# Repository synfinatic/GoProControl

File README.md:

# GoProControl

## About

I wanted an easy way to syncronize my GoPro videos with the data generated from
my data logger.  In the past, I've done this manually with
[DashWare](http://www.dashware.net), but it is a tedious manual process to get
them syncronized.  There had to be a better way!

I realized that many GoPro's (GoPro3 Silver/Black, GoPro4, etc) have built in
WiFi and we all know about the iPhone and Android apps.  So clearly there was a
way to controll them via WiFi.

GoProControl is a simple box you can plug into your car or motorcycle and
connect to your datalogger's digital output or input sensor.  I use the
inexpensive [ESP8266](http://www.esp8266.com/) to control the a GoPro.  In the
future, I hope to be able to control multiple GoPro's like the [GoPro
Remote](http://shop.gopro.com/accessories/smart-remote/ARMTE-002.html) can.

## How it works

GoProControl has 4 pins:

 1. +5-12V
 2. GND
 3. Digital Input 
 4. Digital Ouput
 
When GoProControl is turned on, it will send a signal to the GoPro to also turn
on- which may take a few seconds.  When the Digital Input is connected to
ground (GND) it will tell the GoPro to start recording. 

When the Digital Input is disconnected from ground (floating or +3.3-12V) it
will tell the GoPro to stop recording.  You should configure your GoPro to
auto-off after 60seconds to save battery.

Note, when the Digital Input is connected to ground, the Digital Output will be
driven to 3.3V.  This is so if your data logger does not have an output channel
you can control, you can use a simple toggle switch to both turn on the GoPro
and mark the time when recording started in your data logger using an input
channel on your data logger.

**Note:** If you have the option of powering this by 5 or 12V, use 5V.  If
using your vehicle's battery, be sure it is switched with the ignition to
prevent draining your battery as this circuit uses ~330mA.

## Programming

The GoProControl board has an onboard connector for programming via a FTDI
cable.  This cable should provide 5V of power and can use either 3.3V or 
5V for signalling.

Configure your GoPro WiFi for "App Mode" and define a SSID and WiFi Password.

Before programming your GoProController, you first need to edit 
**src/goprocontrol/goprocontrol.ino** and edit the SSID and WIFI_PASSWORD
to match your GoPro's settings.

In order to program your GoProController, you will need to start the Arduino
application and figure out what serial speed (baud) your ESP8266 communicates
at.  Older boards run at 9600, while newer boards seem to run at 115200.  

Once you have figured out the serial speed, configure Arduino for a 
"Generic ESP8266 Module" and the upload speed to the same speed.  Then, 
with the board powered up:

 1. Press and hold the PROG button
 2. Press and release the RST button
 3. Release the PROG button
 4. Uplaod the sketch via the Arduino application

## Links Links to projects or information that was critical to me creating this
project.  Thank you!

 * [GoProWiFiHack](https://github.com/KonradIT/goprowifihack)
 * [GoProController](https://github.com/joshvillbrandt/GoProController)
 * [GoProHero](https://github.com/joshvillbrandt/goprohero)
 * [GoProControllerUI](https://github.com/joshvillbrandt/GoProControllerUI)

## License

GoProControl is GPLv3

## Trademarks

GoPro, GoPro3 and GoPro4 are trademark [GoPro](http://www.gopro.com).

GoProControl is not affiliated with GoPro in any way.

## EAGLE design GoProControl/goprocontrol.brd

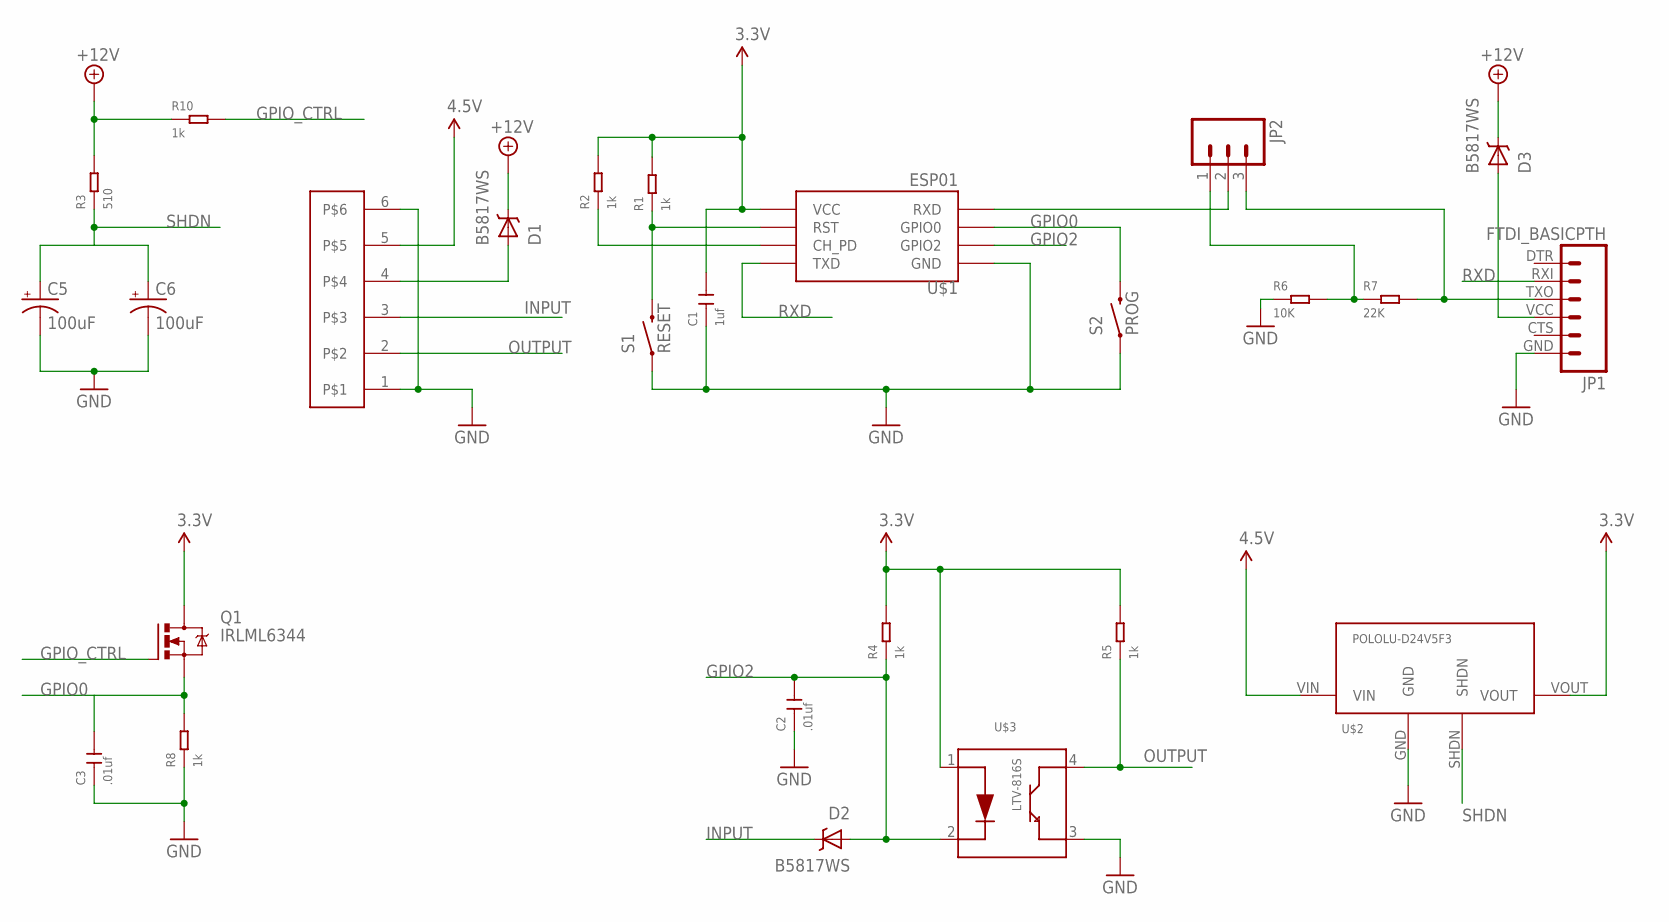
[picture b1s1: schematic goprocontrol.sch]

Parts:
C1: 1uf; C0805
C2, C3: .01uf; C0805
C5, C6: 100uF; CPOL-RADIAL-100UF-25V
D1, D2, D3: B5817WS; SOD-323
JP1: FTDI_BASICPTH; FTDI_BASIC
JP2: M03PTH; 1X03
Q1: IRLML6344; SOT23
R1, R2, R4, R5, R8, R10: 1k; R0805
R3: 510; R0805
R6: 10K; R0805
R7: 22K; R0805
S1: RESET; TACTILE-PTH
S2: PROG; TACTILE-PTH
U$1: ESP01
U$2: POLOLU-D24V5F3; POLOLU-D24V5FX
U$3: LTV-816S; SMD4-2.54-4.6X6.5MM
U$4: TERM-BLOCK-P6-3.5; TERM-6P-3.5

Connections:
3.3V: C1.2, Q1.3 (D), R1.2, R2.2, R4.2, R5.2, U$1.VCC, U$2.VOUT, U$3.1 (ANODE)
3.3V-TX: JP1.TXO (3), JP2.3, R7.2
5V-TX: JP2.1, R6.2, R7.1
+12V: D1.C1 (C), D3.C1 (C), R3.2, R10.1
GND: C1.1, C2.1, C3.1, C5.2 (-), C6.2 (-), JP1.GND (6), R6.1, R8.1, S1.1, S2.1, U$1.GND, U$2.GND, U$3.3 (EMITER), U$4.1, U$4.6
GPIO0: C3.2, Q1.2 (S), R8.2, S2.3 (2), U$1.GPIO0
GPIO2: C2.2, D2.A1 (A), R4.1, U$1.GPIO2, U$3.2 (CATHODE)
GPIO_CTRL: Q1.1 (G), R10.2
INPUT: D2.C1 (C), U$4.3
unnamed: R2.1, U$1.CH_PD
unnamed: R1.1, S1.3 (2), U$1.RST
unnamed: D3.A1 (A), JP1.VCC (4)
unnamed: D1.A1 (A), U$4.4
OUTPUT: R5.1, U$3.4 (COLLECTOR), U$4.2
RXD: JP1.RXI (2), U$1.TX (TXD)
SHDN: C5.1 (+), C6.1 (+), R3.1, U$2.SHDN
TXD: JP2.2, U$1.RX (RXD)
V_BATT: U$2.VIN, U$4.5

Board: 2 copper layers, 26 parts (0 on the bottom side), 18 nets, no tracks yet.

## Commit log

2015-12-06 initial commit. Basic board design, but want to change it
2015-12-06 update board to fit in sv650 ecu decoder box
2015-12-06 added ground planes top & bottom
2015-12-06 v0.1 release
    Fixed outline for term block and labled pins
2015-12-06 v0.2 small tweaks
    - trim board to better fit case
    - verify all DRC/ERC
2015-12-06 Better describe out circuit works
2015-12-06 v0.3
    - heat sink vias are now 0.35mm and have no exposed copper
    - 2x the number of heat sink vias
    - improved labels
2015-12-06 v0.4 fix diode pads
    My old sod-323 and sod-123 pads always seemed a bit wrong/too small
    these new pads are better.
2015-12-07 Helper program to play with ESP8266 using a Teensy 3.x
    Ok, this is lame, but none of my ESP8266 will talk via the
    FTDI cable I have so I ended up using an old Teensy 3.0 I had laying
    around to do the USB->Serial 3.3V converstion. It's lame, but it works.
2015-12-16 Add a 500ma PTC fuse to protect things
2015-12-16 Add pullup on GPIO0 for better reliability and switch to 10K pullups
2015-12-16 small cleanup to .sch
2015-12-16 First pass at some code:
    - Tries to connect to the GoPro WiFi AP
    - Tries to turn on the GoPro
    - When GPIO2 goes low, we start recording
    - When GPIO2 goes high, we stop recording
    Totally untested right now because I seem to be missing the compiler.
    :-/
2015-12-16 Fix & clean up the header file
    Don't need to build our own headers- the HTTP library does that
    Need to rewrite the requests
2015-12-17 Code compiles with ESP8266 v2.0.0 library
2015-12-18 Update PCB to v0.5
    - Switch to using more common 5V FTDI (VCC & signal)
    - Use Schottky diodes to protect reverse polarity and
    to make sure we don't send 12V onto the FTDI VCC line
    - Add 1uF cap to VCC on ESP8266 to stabilize things
    Still would be a good idea to protect against the FTDI
    cable being inserted backwards and putting 5V onto RXD
2015-12-30 Update PCB to v0.6
    - Replace LDO with a switching module
    - Update readme file
2016-01-23 Update board to v0.7
    - Fixes FTDI RX/TX reversal
    - Fixes GPIO2 pullup
    - Rotated termblock
    - Still needs to fix term block part to match
2016-01-24 v0.8 - ordered!
    - Tweaked footprints & labels
    - Changed term block outline to match OST TE 3.5mm
    - Added parts list
2016-03-03 Update code to work better (kinda)
    Code looks like it should work, but it crashes???
2016-03-03 Update PCB to v0.9
    - Just changed silk screen to swap Input/Output labels to
    match the actual pins!
2016-05-24 small board tweaks
2016-06-21 Basic working code
    Seems to work, but board needs to be modified to support
    a automatic shutdown
2016-10-08 renderings of v0.5 of the board
2017-02-26 Redesign board with KiCad
    Utilize 555 timer to do a delayed power off
    for the circuit and the data logger. Removes
    the output signal.
2017-03-12 Design new v2.0 board
    Still ESP8266 based
    Add delaytimer v1.1 circuit for power control
2017-03-12 update BOM
2017-10-15 GoProControl v2.1 ordered
2018-02-18 Rev board to v2.2
    - Switch to using ESP12E
    - Switch to using OptoIsolator + ESP power off detection
    - Using Pot to control power off delay
2018-03-11 v2.3 Board
    - Larger holes for 1x6 connector
    - Move 3.3V regulator out of the way
    - clean up traces
    - remove 3.3V FTDI selector
    - Move Prog switch
    - Better GND/SW-GND for MOSFET
2018-03-24 v2.5 of the board
    - Move main connector to front
    - Use MOSFET to drive GPIO12 like MXL2
    - Larger traces for Switched Ground

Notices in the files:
parts and their libraries:
SparkFun-Connectors: Licensing: Creative Commons ShareAlike 4.0 International - https://creativecommons.org/licenses/by-sa/4.0
SparkFun: Licensing: CC v3.0 Share-Alike You are welcome to use this library for commercial purposes.
